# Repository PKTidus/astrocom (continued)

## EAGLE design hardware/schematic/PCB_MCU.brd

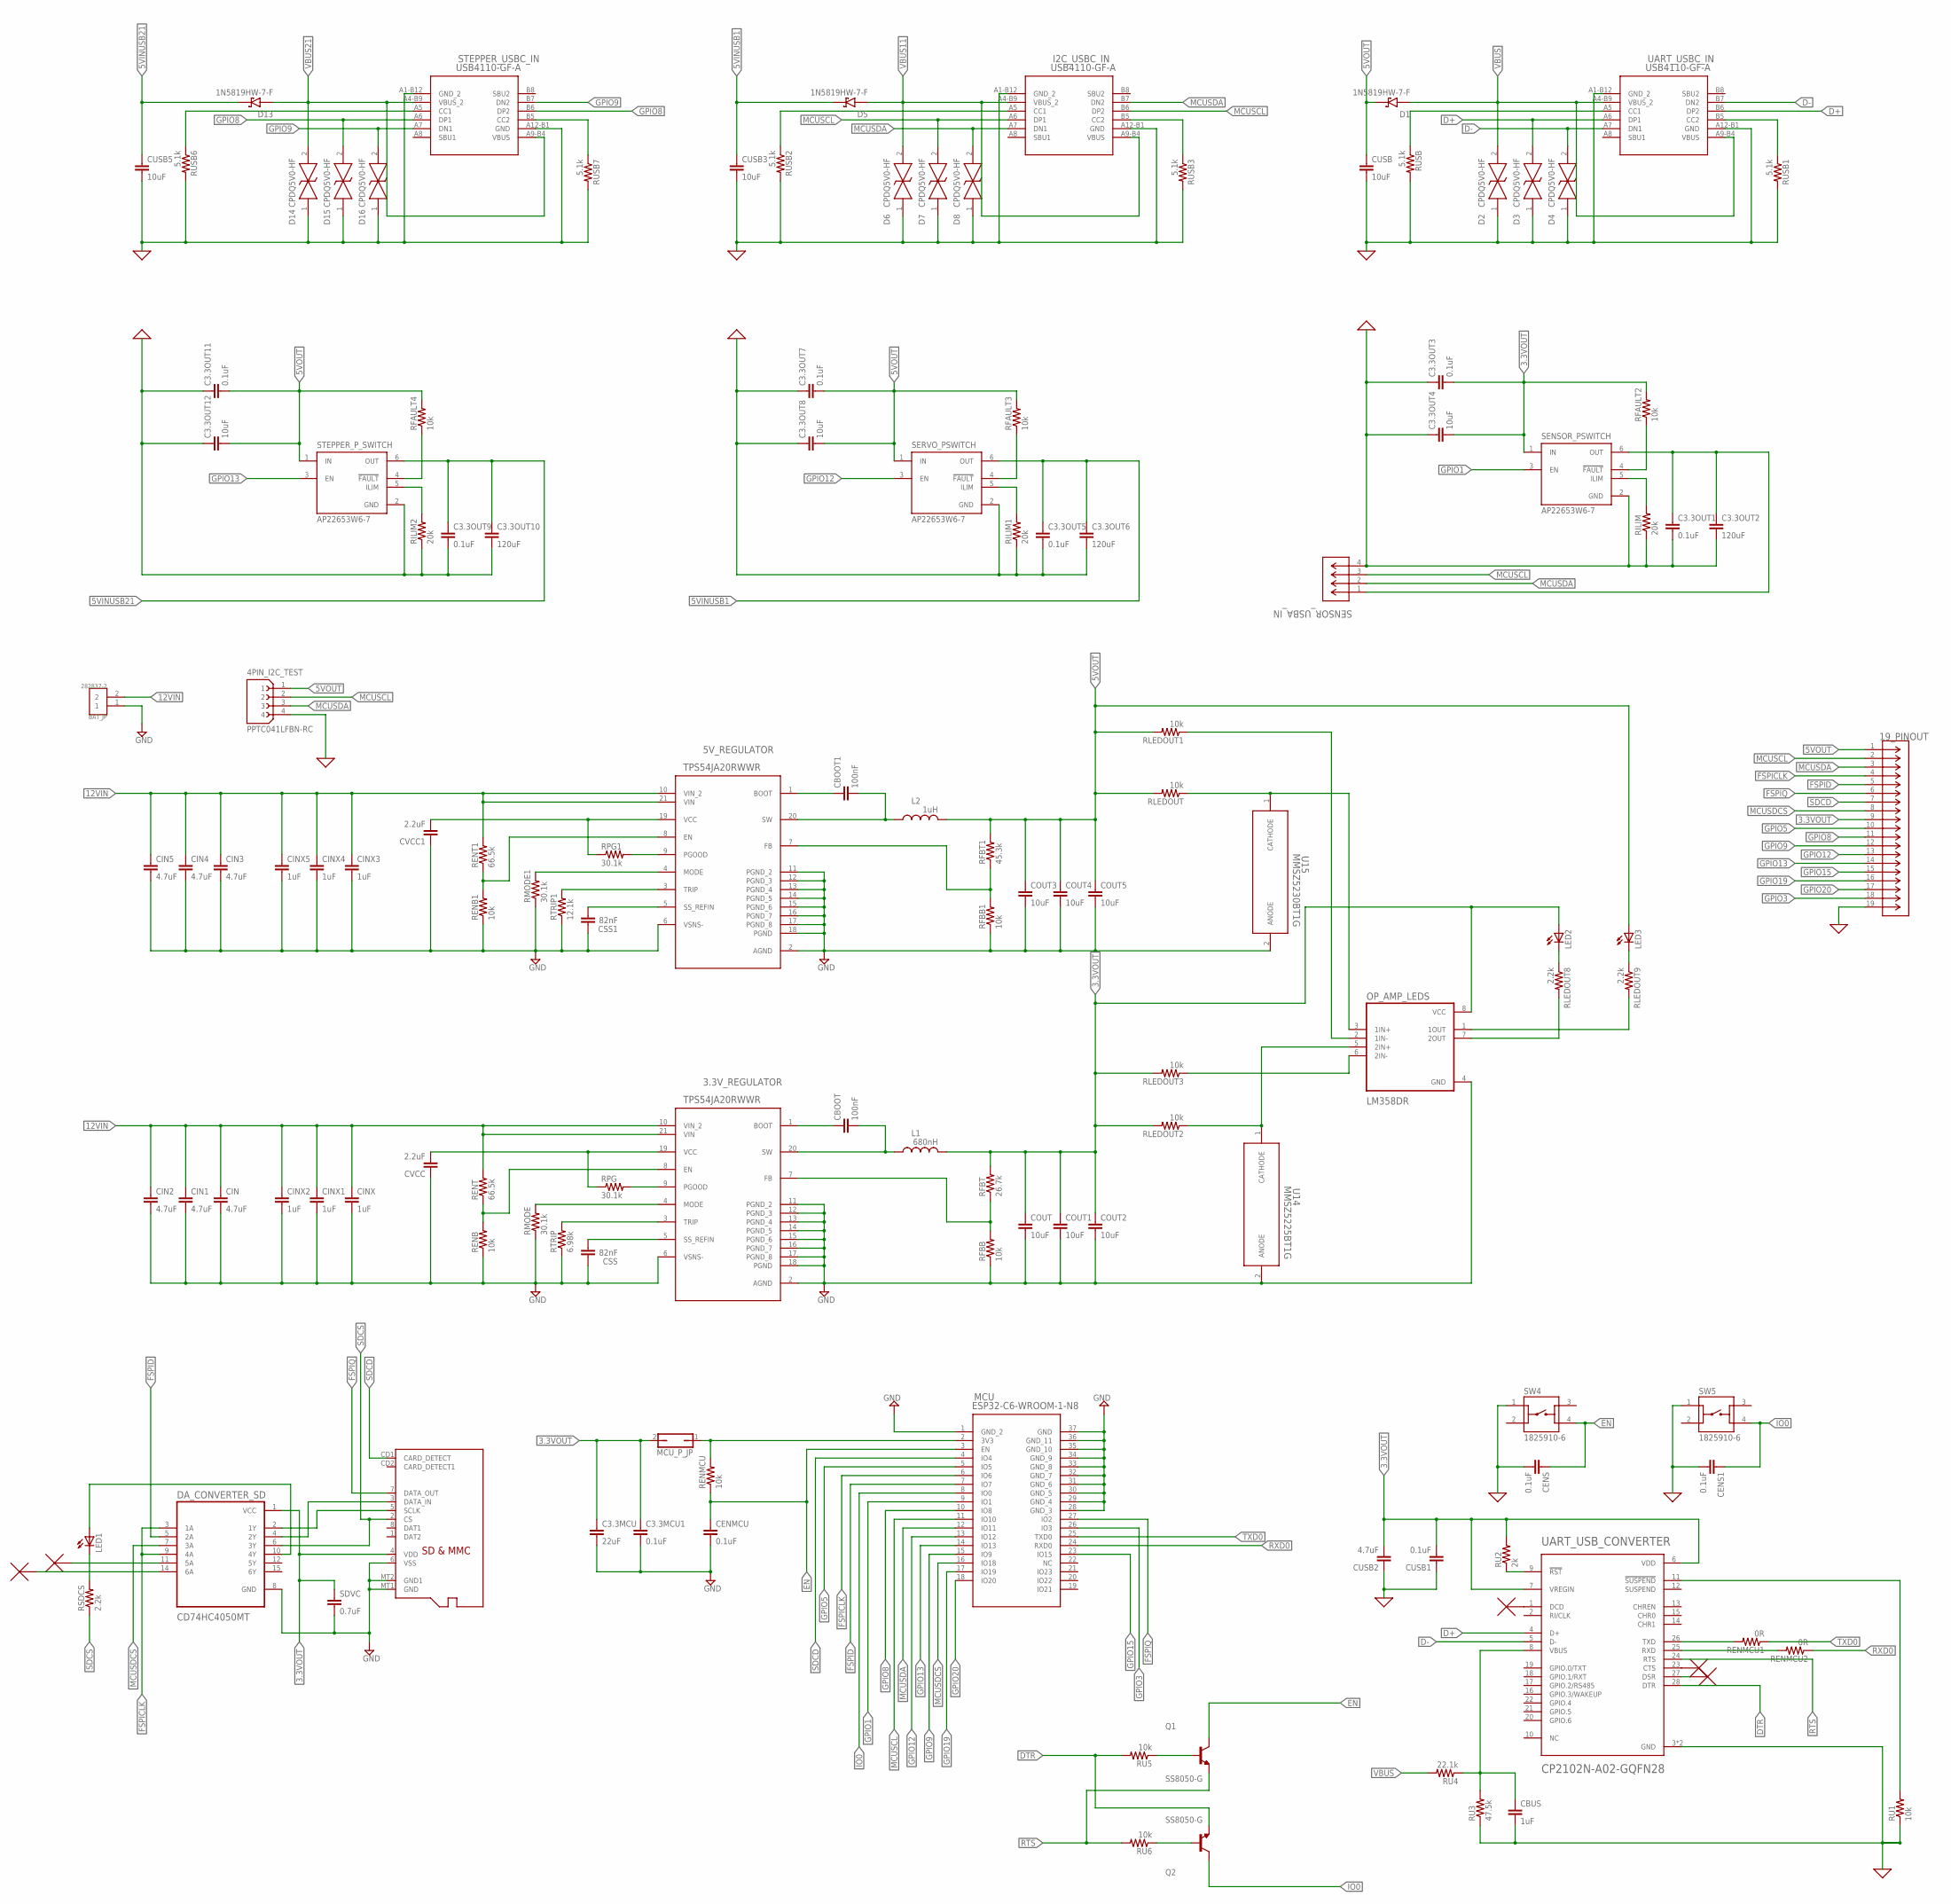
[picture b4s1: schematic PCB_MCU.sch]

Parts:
3.3V_REGULATOR, 5V_REGULATOR: TPS54JA20RWWR; RWW0021A
4PIN_I2C_TEST: PPTC041LFBN-RC; SULLINS_PPTC041LFBN-RC
19_PINOUT: PPTC191LFBN-RC; CONN19_PPTC191LFBN-RC_SUL
BAT_JP: 282837-2; TE_282837-2
C3.3MCU: 22uF; C0805
C3.3MCU1, C3.3OUT1, C3.3OUT3, C3.3OUT5, C3.3OUT7, C3.3OUT9, C3.3OUT11: 0.1uF; C0805
C3.3OUT2, C3.3OUT6, C3.3OUT10: 120uF; C0805
C3.3OUT4, C3.3OUT8, C3.3OUT12: 10uF; C0805
CBOOT, CBOOT1: 100nF; C0805
CBUS: 1uF; C0805
CENMCU: 0.1uF; C0805
CENS, CENS1: 0.1uF; C0805
CIN, CIN1, CIN2, CIN3, CIN4, CIN5: 4.7uF; C0805
CINX, CINX1, CINX2, CINX3, CINX4, CINX5: 1uF; C0805
COUT, COUT1, COUT2, COUT3, COUT4, COUT5: 10uF; C0805
CSS, CSS1: 82nF; C0805
CUSB, CUSB3, CUSB5: 10uF; C0805
CUSB1: 0.1uF; C0805
CUSB2: 4.7uF; C0805
CVCC, CVCC1: 2.2uF; C0805
D1, D5, D13: 1N5819HW-7-F; SOD3715X145N
D2, D3, D4, D6, D7, D8, D14, D15, D16: CPDQ5V0-HF; MBTB-D-SOD-923F-IMP-0402
DA_CONVERTER_SD: CD74HC4050MT; SOIC127P600X175-16N
I2C_USBC_IN: USB4110-GF-A; USB4110-GF-A_GCT
L1: 680nH; 6000-XXXX-RC
L2: 1uH; 6000-XXXX-RC
LED1, LED2, LED3: LED; SMARTLED-TTW
MCU: ESP32-C6-WROOM-1-N8; MOD28_ESP32-C6-WROOM-1_EXP
MCU_P_JP: JP1Q; JP1
OP_AMP_LEDS: LM358DR; SOIC127P599X175-8N
Q1, Q2: SS8050-G; TRANS_SS8050-G
RENB, RENB1: 10k; M0805
RENMCU: 10k; M0805
RENMCU1, RENMCU2: 0R; M0805
RENT, RENT1: 66.5k; M0805
RFAULT2, RFAULT3, RFAULT4: 10k; M0805
RFBB, RFBB1: 10k; M0805
RFBT: 26.7k; M0805
RFBT1: 45.3k; M0805
RILIM, RILIM1, RILIM2: 20k; M0805
RLEDOUT, RLEDOUT1, RLEDOUT2, RLEDOUT3: 10k; M0805
RLEDOUT8, RLEDOUT9: 2.2k; M0805
RMODE, RMODE1: 30.1k; M0805
RPG, RPG1: 30.1k; M0805
RSDCS: 2.2k; M0805
RTRIP: 6.98k; M0805
RTRIP1: 12.1k; M0805
RU1, RU5, RU6: 10k; M0805
RU2: 2k; M0805
RU3: 47.5k; M0805
RU4: 22.1k; M0805
RUSB, RUSB1, RUSB2, RUSB3, RUSB6, RUSB7: 5.1k; M0805
SDVC: 0.7uF; C0805
SD_CONNECTOR: MICROSD
SENSOR_PSWITCH: AP22653W6-7; SOT95P280X145-6N
SENSOR_USBA_IN: USB-AP-S-RA-SMT; CONN_USB-AP-S-RA-SMT_ADM
SERVO_PSWITCH: AP22653W6-7; SOT95P280X145-6N
STEPPER_P_SWITCH: AP22653W6-7; SOT95P280X145-6N
STEPPER_USBC_IN: USB4110-GF-A; USB4110-GF-A_GCT
SW4, SW5: 1825910-6; SW_1825910-6-4
U14: MMSZ5225BT1G; SOD-123_ONS
U15: MMSZ5230BT1G; SOD-123_ONS
UART_USBC_IN: USB4110-GF-A; USB4110-GF-A_GCT
UART_USB_CONVERTER: CP2102N-A02-GQFN28; QFN50P500X500X80-29N

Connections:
0: 4PIN_I2C_TEST.4, 19_PINOUT.19, C3.3OUT1.2, C3.3OUT2.2, C3.3OUT3.1, C3.3OUT4.1, C3.3OUT5.2, C3.3OUT6.2, C3.3OUT7.1, C3.3OUT8.1, C3.3OUT9.2, C3.3OUT10.2, C3.3OUT11.1, C3.3OUT12.1, CBUS.2, CENS.2, CENS1.2, CUSB.2, CUSB1.1, CUSB2.1, CUSB3.2, CUSB5.2, D2.1 (K), D3.1 (K), D4.1 (K), D6.1 (K), D7.1 (K), D8.1 (K), D14.1 (K), D15.1 (K), D16.1 (K), I2C_USBC_IN.A1-B12 (GND_2), I2C_USBC_IN.A12-B1 (GND), RILIM.1, RILIM1.1, RILIM2.1, RU1.1, RU3.1, RUSB.2, RUSB1.2, RUSB2.2, RUSB3.2, RUSB6.2, RUSB7.2, SENSOR_PSWITCH.2 (GND), SENSOR_USBA_IN.4, SERVO_PSWITCH.2 (GND), STEPPER_P_SWITCH.2 (GND), STEPPER_USBC_IN.A1-B12 (GND_2), STEPPER_USBC_IN.A12-B1 (GND), SW4.1, SW5.1, UART_USBC_IN.A1-B12 (GND_2), UART_USBC_IN.A12-B1 (GND), UART_USB_CONVERTER.3 (GND), UART_USB_CONVERTER.29 (GND)
3.3VOUT: 19_PINOUT.9, C3.3MCU.1, C3.3MCU1.1, C3.3OUT3.2, C3.3OUT4.2, COUT.1, COUT1.1, COUT2.1, CUSB1.2, CUSB2.2, DA_CONVERTER_SD.1 (VCC), L1.2, LED2.A@1 (A), MCU_P_JP.2, OP_AMP_LEDS.8 (VCC), RFAULT2.2, RFBT.2, RLEDOUT2.2, RLEDOUT3.2, RU2.2, SDVC.1, SD_CONNECTOR.4 (VDD), SENSOR_PSWITCH.1 (IN), UART_USB_CONVERTER.6 (VDD), UART_USB_CONVERTER.7 (VREGIN)
5VINUSB1: C3.3OUT5.1, C3.3OUT6.1, CUSB3.1, D5.C (K), SERVO_PSWITCH.6 (OUT)
5VINUSB21: C3.3OUT9.1, C3.3OUT10.1, CUSB5.1, D13.C (K), STEPPER_P_SWITCH.6 (OUT)
5VOUT: 4PIN_I2C_TEST.1, 19_PINOUT.1, C3.3OUT7.2, C3.3OUT8.2, C3.3OUT11.2, C3.3OUT12.2, COUT3.1, COUT4.1, COUT5.1, CUSB.1, D1.C (K), L2.2, LED3.A@1 (A), RFAULT3.2, RFAULT4.2, RFBT1.2, RLEDOUT.2, RLEDOUT1.2, SERVO_PSWITCH.1 (IN), STEPPER_P_SWITCH.1 (IN)
12VIN: 3.3V_REGULATOR.10 (VIN_2), 3.3V_REGULATOR.21 (VIN), 5V_REGULATOR.10 (VIN_2), 5V_REGULATOR.21 (VIN), BAT_JP.2, CIN.1, CIN1.1, CIN2.1, CIN3.1, CIN4.1, CIN5.1, CINX.1, CINX1.1, CINX2.1, CINX3.1, CINX4.1, CINX5.1, RENT.2, RENT1.2
D+: D3.2 (A), UART_USBC_IN.A6 (DP1), UART_USBC_IN.B6 (DP2), UART_USB_CONVERTER.4 (D+)
D-: D4.2 (A), UART_USBC_IN.A7 (DN1), UART_USBC_IN.B7 (DN2), UART_USB_CONVERTER.5 (D-)
DTR: Q2.2 (E), RU5.2, UART_USB_CONVERTER.28 (DTR)
EN: CENMCU.1, CENS.1, MCU.3 (EN), Q1.3 (C), RENMCU.1, SW4.4
FSPICLK: 19_PINOUT.4, DA_CONVERTER_SD.3 (1A), DA_CONVERTER_SD.9 (4A), MCU.6 (IO6)
FSPID: 19_PINOUT.5, DA_CONVERTER_SD.5 (2A), MCU.7 (IO7)
FSPIQ: 19_PINOUT.6, MCU.27 (IO2), SD_CONNECTOR.7 (DATA_OUT)
GND: 3.3V_REGULATOR.2 (AGND), 3.3V_REGULATOR.6 (VSNS-), 3.3V_REGULATOR.11 (PGND_2), 3.3V_REGULATOR.12 (PGND_3), 3.3V_REGULATOR.13 (PGND_4), 3.3V_REGULATOR.14 (PGND_5), 3.3V_REGULATOR.15 (PGND_6), 3.3V_REGULATOR.16 (PGND_7), 3.3V_REGULATOR.17 (PGND_8), 3.3V_REGULATOR.18 (PGND), 5V_REGULATOR.2 (AGND), 5V_REGULATOR.6 (VSNS-), 5V_REGULATOR.11 (PGND_2), 5V_REGULATOR.12 (PGND_3), 5V_REGULATOR.13 (PGND_4), 5V_REGULATOR.14 (PGND_5), 5V_REGULATOR.15 (PGND_6), 5V_REGULATOR.16 (PGND_7), 5V_REGULATOR.17 (PGND_8), 5V_REGULATOR.18 (PGND), BAT_JP.1, C3.3MCU.2, C3.3MCU1.2, CENMCU.2, CIN.2, CIN1.2, CIN2.2, CIN3.2, CIN4.2, CIN5.2, CINX.2, CINX1.2, CINX2.2, CINX3.2, CINX4.2, CINX5.2, COUT.2, COUT1.2, COUT2.2, COUT3.2, COUT4.2, COUT5.2, CSS.1, CSS1.1, CVCC.1, CVCC1.1, DA_CONVERTER_SD.8 (GND), MCU.1 (GND_2), MCU.28 (GND_3), MCU.29 (GND_4), MCU.30 (GND_5), MCU.31 (GND_6), MCU.32 (GND_7), MCU.33 (GND_8), MCU.34 (GND_9), MCU.35 (GND_10), MCU.36 (GND_11), MCU.37 (GND), OP_AMP_LEDS.4 (GND), RENB.1, RENB1.1, RFBB.1, RFBB1.1, RMODE.1, RMODE1.1, RTRIP.1, RTRIP1.1, SDVC.2, SD_CONNECTOR.6 (VSS), SD_CONNECTOR.MT1 (GND), SD_CONNECTOR.MT2 (GND1), U14.2 (ANODE), U15.2 (ANODE)
GPIO1: MCU.9 (IO1), SENSOR_PSWITCH.3 (EN)
GPIO3: 19_PINOUT.18, MCU.26 (IO3)
GPIO5: 19_PINOUT.10, MCU.5 (IO5)
GPIO8: 19_PINOUT.11, D15.2 (A), MCU.10 (IO8), STEPPER_USBC_IN.A6 (DP1), STEPPER_USBC_IN.B6 (DP2)
GPIO9: 19_PINOUT.12, D16.2 (A), MCU.15 (IO9), STEPPER_USBC_IN.A7 (DN1), STEPPER_USBC_IN.B7 (DN2)
GPIO12: 19_PINOUT.13, MCU.13 (IO12), SERVO_PSWITCH.3 (EN)
GPIO13: 19_PINOUT.14, MCU.14 (IO13), STEPPER_P_SWITCH.3 (EN)
GPIO15: 19_PINOUT.15, MCU.23 (IO15)
GPIO19: 19_PINOUT.16, MCU.17 (IO19)
GPIO20: 19_PINOUT.17, MCU.18 (IO20)
IO0: CENS1.1, MCU.8 (IO0), Q2.3 (C), SW5.4
MCUSCL: 4PIN_I2C_TEST.2, 19_PINOUT.2, D7.2 (A), I2C_USBC_IN.A6 (DP1), I2C_USBC_IN.B6 (DP2), MCU.11 (IO10), SENSOR_USBA_IN.3
MCUSDA: 4PIN_I2C_TEST.3, 19_PINOUT.3, D8.2 (A), I2C_USBC_IN.A7 (DN1), I2C_USBC_IN.B7 (DN2), MCU.12 (IO11), SENSOR_USBA_IN.2
MCUSDCS: 19_PINOUT.8, DA_CONVERTER_SD.7 (3A), MCU.16 (IO18)
unnamed: 3.3V_REGULATOR.1 (BOOT), CBOOT.1
unnamed: 3.3V_REGULATOR.20 (SW), CBOOT.2, L1.1
unnamed: 3.3V_REGULATOR.19 (VCC), CVCC.2, RPG.1
unnamed: 3.3V_REGULATOR.9 (PGOOD), RPG.2
unnamed: 3.3V_REGULATOR.8 (EN), RENB.2, RENT.1
unnamed: 3.3V_REGULATOR.4 (MODE), RMODE.2
unnamed: 3.3V_REGULATOR.3 (TRIP), RTRIP.2
unnamed: 3.3V_REGULATOR.5 (SS_REFIN), CSS.2
unnamed: 3.3V_REGULATOR.7 (FB), RFBB.2, RFBT.1
unnamed: RENMCU1.2, UART_USB_CONVERTER.26 (TXD)
unnamed: 5V_REGULATOR.1 (BOOT), CBOOT1.1
unnamed: RENMCU2.2, UART_USB_CONVERTER.25 (RXD)
unnamed: 5V_REGULATOR.20 (SW), CBOOT1.2, L2.1
unnamed: 5V_REGULATOR.19 (VCC), CVCC1.2, RPG1.1
unnamed: 5V_REGULATOR.9 (PGOOD), RPG1.2
unnamed: 5V_REGULATOR.4 (MODE), RMODE1.2
unnamed: 5V_REGULATOR.3 (TRIP), RTRIP1.2
unnamed: 5V_REGULATOR.5 (SS_REFIN), CSS1.2
unnamed: 5V_REGULATOR.8 (EN), RENB1.2, RENT1.1
unnamed: LED3.C@1 (C), RLEDOUT9.1
unnamed: 5V_REGULATOR.7 (FB), RFBB1.2, RFBT1.1
unnamed: RU1.2, UART_USB_CONVERTER.11 (!SUSPEND)
unnamed: RU2.1, UART_USB_CONVERTER.9 (!RST)
unnamed: CBUS.1, RU3.2, RU4.1, UART_USB_CONVERTER.8 (VBUS)
unnamed: Q1.1 (B), RU5.1
unnamed: Q2.1 (B), RU6.1
unnamed: MCU.2 (3V3), MCU_P_JP.1, RENMCU.2
unnamed: RUSB.1, UART_USBC_IN.A5 (CC1)
unnamed: LED1.C@1 (C), RSDCS.2
unnamed: DA_CONVERTER_SD.10 (4Y), LED1.A@1 (A)
unnamed: RUSB1.1, UART_USBC_IN.B5 (CC2)
unnamed: DA_CONVERTER_SD.2 (1Y), SD_CONNECTOR.5 (SCLK)
unnamed: RILIM.2, SENSOR_PSWITCH.5 (ILIM)
unnamed: DA_CONVERTER_SD.4 (2Y), SD_CONNECTOR.3 (DATA_IN)
unnamed: C3.3OUT1.1, C3.3OUT2.1, SENSOR_PSWITCH.6 (OUT), SENSOR_USBA_IN.1
unnamed: RFAULT2.1, SENSOR_PSWITCH.4 (!FAULT)
unnamed: I2C_USBC_IN.A5 (CC1), RUSB2.1
unnamed: I2C_USBC_IN.B5 (CC2), RUSB3.1
unnamed: RUSB6.1, STEPPER_USBC_IN.A5 (CC1)
unnamed: RILIM1.2, SERVO_PSWITCH.5 (ILIM)
unnamed: RFAULT3.1, SERVO_PSWITCH.4 (!FAULT)
unnamed: RUSB7.1, STEPPER_USBC_IN.B5 (CC2)
unnamed: RILIM2.2, STEPPER_P_SWITCH.5 (ILIM)
unnamed: RFAULT4.1, STEPPER_P_SWITCH.4 (!FAULT)
unnamed: OP_AMP_LEDS.5 (2IN+), RLEDOUT2.1, U14.1 (CATHODE)
unnamed: OP_AMP_LEDS.6 (2IN-), RLEDOUT3.1
unnamed: OP_AMP_LEDS.7 (2OUT), RLEDOUT8.2
unnamed: OP_AMP_LEDS.3 (1IN+), RLEDOUT.1, U15.1 (CATHODE)
unnamed: OP_AMP_LEDS.2 (1IN-), RLEDOUT1.1
unnamed: OP_AMP_LEDS.1 (1OUT), RLEDOUT9.2
unnamed: LED2.C@1 (C), RLEDOUT8.1
RTS: Q1.2 (E), RU6.2, UART_USB_CONVERTER.24 (RTS)
RXD0: MCU.24 (RXD0), RENMCU2.1
SDCD: 19_PINOUT.7, MCU.4 (IO4), SD_CONNECTOR.CD1 (CARD_DETECT)
SDCS: DA_CONVERTER_SD.6 (3Y), RSDCS.1, SD_CONNECTOR.2 (CS)
TXD0: MCU.25 (TXD0), RENMCU1.1
VBUS: D1.A, D2.2 (A), RU4.2, UART_USBC_IN.A4-B9 (VBUS_2), UART_USBC_IN.A9-B4 (VBUS)
VBUS11: D5.A, D6.2 (A), I2C_USBC_IN.A4-B9 (VBUS_2), I2C_USBC_IN.A9-B4 (VBUS)
VBUS21: D13.A, D14.2 (A), STEPPER_USBC_IN.A4-B9 (VBUS_2), STEPPER_USBC_IN.A9-B4 (VBUS)

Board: 2 copper layers, 131 parts (0 on the bottom side), 87 nets, no tracks yet.

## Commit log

2023-09-01 Starting files
2023-09-11 Add some pictures
2023-09-13 Add D&C and sponsor link
2023-09-13 Fixed sponsor not being centered, need to add padding at bottom
2023-09-15 Add special thanks and SD1 document
2023-10-06 Restructure
2023-10-06 Restructure with placeholder files
2023-10-06 Website update, add assets
2023-10-13 Libraries updated
2023-10-13 Schematic updates
2023-10-14 Schematics updates
2023-10-14 Servo Updated
2023-10-20 Hardware and Documents updates
2023-10-20 CAD updates
2023-10-23 Added regulators and SD Card. Needs major work
2023-10-24 Updates Schematic
2023-10-24 Added Silkscreen text, widened approiate traces, added mounting holes
2023-10-24 Altium Updates
2023-10-24 gitignore
2023-10-24 change folder name
2023-10-25 Add Altium Libraries
2023-10-26 Add files via upload
    Added SJs and reworked some of the layout
2023-10-26 updated with Dr.Week's advice
2023-10-27 Updated Schematic with Dr.Week's Advice
2023-10-27 Remove libraries
2023-10-27 imported from eagle
2023-10-27 imported to altium from Eagle
2023-10-27 passing over to binh
2023-10-27 Added 3.3Vreg
2023-10-27 added 3.3v regulator
2023-11-03 Add files via upload
    Updated MCU
2023-11-05 Added everything to board, still need to route and check with Dr.Weeks about ESD and protection devices
2023-11-05 Added everything to board, need to route and revise with Dr.Weeks
2023-11-07 Started Routing, corrected a few things on the sch
2023-11-07 Did more routing in preparation for Dr. Weeks meeting. Added notes for meeting in discord. Still need to add polygon pours, route/edit pinouts, and change trace size for high-current traces.
2023-11-07 Sensor PCB
2023-11-07 Create PCB_Project
2023-11-07 Add schematic
2023-11-07 New schematic
2023-11-07 Servo_Schematic
2023-11-07 Update Servo
2023-11-07 Did more routing, upsized traces for power rails, route some of the pintouts. Still needs to upsize the 5v lines and confirm design with Dr.Weeks
2023-11-10 did it
2023-11-10 Revert ""
    This reverts commit ac9c56ac2cc19b43639679a98ae752f1438a7eaf.
2023-11-14 LPiece Added
    Lpiece
2023-11-14 Lpiece
2023-11-17 Nearly finished, routed, added stitching, need to clear errors and send out for fab
2023-11-18 Routed board and got to 80% complete. Need to add resistors and jumpers
2023-11-18 Add files via upload
    TRYING TO FIX VERSION CONTROL
2023-11-18 Revert ""
    This reverts commit d8623637ee42012c651c6b58d0cd1c96efef24c9.
2023-11-19 Reduced DRC errors to 29
2023-11-19 Down to 25 errors, added via stitching on edge of board. Still need to rework the mounting holes
2023-11-19 Reduced number of errors, all remaining errors are due to components themselves
2023-11-20 Fixed the SD card PO
2023-11-21 Test for binh, DRC is bugged out
2023-11-21 Reduced DRC Errors to 99
2023-11-21 Add rules
2024-01-17 Update 01/16/24
2024-01-18 Powerpoint
2024-01-24 Moved USB and Traces down a bit to accomodate sun shade fins
2024-01-27 CAD Update
2024-01-27 CAD and software update
2024-01-27 servo cad update
2024-01-27 servo update with arm
2024-01-27 Servo dwg
2024-01-27 bearing update
2024-01-27 Servo bearing update
2024-01-27 Altium Missing file update
2024-01-28 Sensor PCB updates
2024-01-28 servo housing updates
2024-01-28 Servo Housing Top update
2024-01-28 L pieces updates
2024-01-29 sensor code
2024-01-29 New Servo code updates
2024-01-29 servo housing
2024-01-29 resize cad
2024-01-30 Bearing updates
2024-01-30 bearing stl update
2024-02-01 bearing
2024-02-03 servo code
2024-02-05 Add files via upload
    Cv_Axle Update
2024-02-05 bearing and servo housing
2024-02-05 Add files via upload
    Changed CV_Axle diameter from 24.75mm to 25.5 mm
2024-02-06 servo housing update
2024-02-06 servo code update
2024-02-07 design update
2024-02-07 remove files
2024-02-08 cad changes
2024-02-15 Remove placeholders, add astromsg project
2024-02-17 Update astromsg
2024-02-19 changed io8&9 and added jumpers
2024-02-20 SD connector
2024-02-21 interrupt code for sensors
2024-02-21 Stepper
2024-02-22 Add files via upload
    added stand for the mirror tower turntable
2024-02-23 Add files via upload
    updated stand to make it printable
2024-02-23 SCHEMATIC
2024-02-24 Revert "Update PCB_MCU.SchDocPreview"
    This reverts commit ddec6d07e2fb772a69af23b70bcde731b64560f2.
2024-02-24 Revert ""
    This reverts commit 31b8cfdc3627c0a10d7378ba0c8c8245825f1724.
2024-02-24 Revert ""
    This reverts commit 0a18cf6965cb90f89b2af8d74de933828272ad35.
2024-02-24 Revert "SCHEMATIC"
    This reverts commit b3244c10bdc3b370953aed1d92168c0c535bb831.
2024-02-24 Revert "Revert "SCHEMATIC""
    This reverts commit 2732cb36103b64c9210c05b73c3fbde493747707.
2024-02-24 Revert "Revert """
    This reverts commit 8e956d1836c0f8c36de412ee7d657c7c1d2db0cf.
2024-02-24 Revert "Revert """
    This reverts commit 58cbc57fabd00ab80dc60cc66da1a14e84a25dc3.
2024-02-24 Revert "Revert "Update PCB_MCU.SchDocPreview""
    This reverts commit 89693c5361c2808f3b457fc1f309fa40f13faff4.
2024-02-24 MCU PCB
2024-02-24 Messaging real + converter js
2024-02-29 MCU Board
    Increased trace width of USBs
    updated schematic
2024-03-02 connected code with servo and sensor
2024-03-02 Servo sensor testing project added to software dir
2024-03-05 updated code from tuesday with servo/stepper math
2024-03-06 updated code with servo motor testing
2024-03-10 updated code from saturday
2024-03-14 updated astrocom code with mirror in vertical direction
2024-03-14 Website upgrade
2024-03-14 updated code with mirror working in vertical and horizontal direction
2024-03-27 Add midterm demo video to website
2024-03-29 updated integrated code with new freq and full comments
2024-04-03 Add conference paper to website
2024-04-03 updated conference paper and website
2024-04-03 comment tweaking on integrated code
2024-04-04 Website update with cdr, final pres etc
2024-04-06 updated index for website
2024-04-06 Website new tabs and pdf presentation
2024-04-06 File cleaning
2024-04-07 added sd2 combined and final demo video to website files
2024-04-11 updated combined code
2024-04-17 Cleanup
2024-04-17 Change
2024-04-19 Demo pictures and github link on website
